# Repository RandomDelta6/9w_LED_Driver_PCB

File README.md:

# Introduction

This a power supply that feeds mains to power a 9w led array for general illumination (60W Incandescent equivalent). The circuit is based around the Sic 9752 microcontroller which provides Active PFC (Power Factor Correction) for high power factor and low THD. Its also a non isolated buck driver which allows it have >95% power efficiency and a simple compact circuit. It also features over current protection, over temperature protection, short circuit protection, low startup and operating current and flicker free continuous mode operation. It also incorporates QoL features such as soft start and a discharge resistor to ensure no ghost glow and fast cutoff when switched off.

# Schematic

# PCB

PCB Front View

PCB Back View

# Usage

Wave Solder all SMD components on the front side of the board. Then, thread in the THT components through their respective through holes from the back side and solder on to the front side. Snip off excess length of the legs after soldering. Solder a wire from +ve pad of LED grid to +ve output pad of this pcb. Solder a wire from -ve pad of LED grid to -ve output pad of this pcb. Thread in the wire through the hole from the back of the pcb and solder it on the front side.

For B22 Base, thread the free legs of the fusible resistors through the holes on the bottom of the base. Apply sufficient amount of solder to make the contact points for the bulb with the electrical socket. Snip off excess length of the legs after soldering. For E26/27 Base, solder one leg to the bottom contact of the base and solder the other leg to the side contact of the base.

This pcb is intended for LED bulbs with an opaque lower half body and translucent/ transparent cap (as pictured above) and not for the ones featuring a fully transparent or translucent body. This pcb is tuned for a 220V AC Power Input. This pcb expects a DOB grid of LED chips only, of 9W dissipation on the output and not a DOB board featuring other components (as illustrated above). DOB boards typically have an aluminimum substrate to aid in heat dissipation and are thermally coupled to an aluminium disc for larger thermal mass and surface area to aid in heat dissipation. The pcb must be suspended or have the front surface isolated by a layer of Kapton tape incase the opaque lower half of the bulb features aluminium plating for heat dissipation. The pcb must be completely isolated electrically from any other metal surfaces except as specified in the first paragraph of usage directions.

# Notes

Although I am pretty confident the board should work, please have the board verified by a professional before deploying in production. I am not particularly sure about the value of C5. C6 and R8 are not to be connected for intended use as a 9w LED Driver PCB.

Couldn't find a proper model for Inductor L2, so it is missing on the back view of the PCB. Didn't bother with it since it doesn't really matter much. Couldn't find the proper model for Film Capacitor C1. In reality it would look like a brown pillow with the same pin to pin footprint as in the back view of pcb.

This project was initially made with Kicad 5.1.10 and later updated on Kicad 7.0

While exporting for fabrication the back solder mask layer may be ignored to save on manufacturing costs as it serves no purpose.

# Disclaimer
This board has not been printed and tested physically to verify functionality. I do not assume any liability for the materials, information and opinions provided on, or available through, this project. I disclaim any liability for injury, death or damages resulting from the use thereof. This board is classified as “HOT” since it takes in mains power. Modify or work on it at your own risk and maintain proper safety procedures while physically handling such circuits.

# Licensing
All PCB design files and hardware are released under the [Creative Commons Attribution Share Alike 4.0 license](https://choosealicense.com/licenses/cc-by-sa-4.0/).

All other software is released under the [GNU General Public License v3.0](https://choosealicense.com/licenses/gpl-3.0/).

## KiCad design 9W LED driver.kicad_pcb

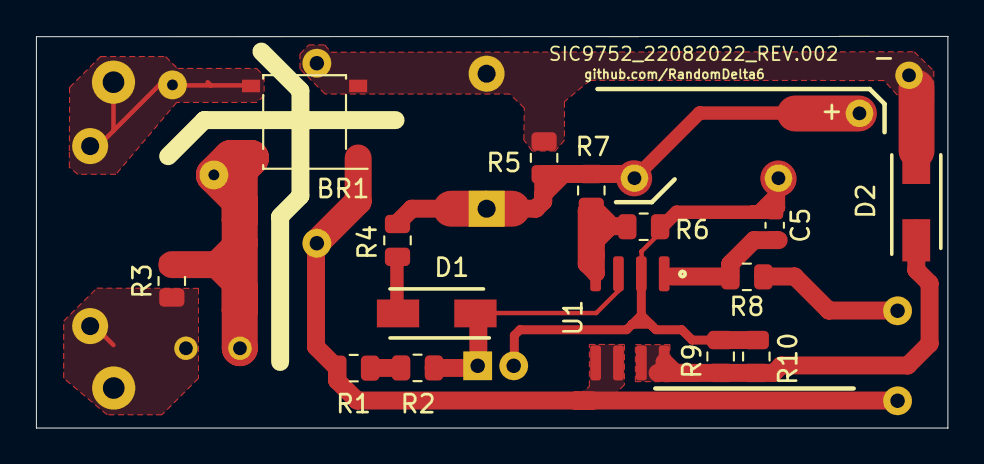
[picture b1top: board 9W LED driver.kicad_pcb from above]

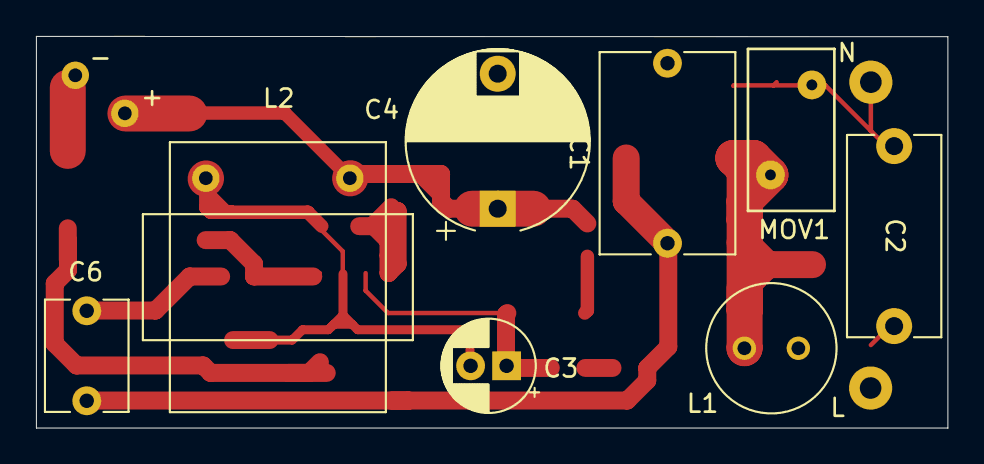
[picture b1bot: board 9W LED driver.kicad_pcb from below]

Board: 2 copper layers, 50.6 x 21.8 mm, 27 parts (10 on the bottom side), 14 nets.

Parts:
+: +ve Output; Pad
-: -ve Output; Pad
BR1: D_Bridge_+-AA; Diode_Bridge_Diotec_ABS
C1: 3.3uF 400V; C_Rect_L11.0mm_W7.3mm_P10.00mm_MKT
C2: 0.01uF 400V; C_Disc_D11.0mm_W5.0mm_P10.00mm
C3: 4.7uF 50V; CP_Radial_D5.0mm_P2.00mm
C4: 82uF 80V; CP_Radial_D10.0mm_P7.50mm
C5: 220nF 50V; C_0603_1608Metric
C6: C_Disc_D6.0mm_W4.4mm_P5.00mm
D1, D2: D ES1J; DIOM5227X250N
F1, F2: 56.00 ± 5%; R_Axial_DIN0411_L9.9mm_D3.6mm_P12.70mm_Horizontal
L1: 7mH; L_Radial_D7.0mm_P3.00mm
L2: 2.1mH; Inductor_Transformer
MOV1: 320V 100pF; RV_Disc_D9mm_W4.8mm_P5mm
R1, R2: 330K; R_0805_2012Metric
R3: 47K; R_0805_2012Metric
R4: 24K; R_0805_2012Metric
R5, R6: 150K; R_0805_2012Metric
R7: 210; R_0805_2012Metric
R8: R_0805_2012Metric
R9, R10: 3.3; R_0805_2012Metric
U1: Sic9752; SOIC-8_3.9x4.9mm_P1.27mm

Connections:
+ve_Rail: BR1.1 (+), C1.1, C6.2, R1.1, U1.5 (DRAIN), U1.6 (DRAIN)
+ve_output: +.1, C4.1, L2.1, R4.1, R5.1, R7.2
GNDS: -.1, BR1.2 (-), C1.2, C4.2, D2.2 (A), R5.2
unnamed: BR1.3, C2.2, F2.1, MOV1.1
unnamed: BR1.4, L1.2, MOV1.2, R3.2
unnamed: C2.1, F1.1, L1.1, R3.1
unnamed: C6.1, R8.1
unnamed: D1.2 (A), R4.2
unnamed: C3.1, D1.1 (K), R2.2, U1.3 (VDD)
unnamed: D2.1 (K), R9.1, R10.1, U1.7 (ISEN), U1.8 (ISEN)
unnamed: R1.2, R2.1
unnamed: C5.2, R8.2, U1.1 (COMP)
unnamed: R6.1, R7.1, U1.4 (FB)
unnamed: C3.2, C5.1, L2.2, R6.2, R9.2, R10.2, U1.2 (GND)

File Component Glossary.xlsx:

Sl. No. | Notation | Type | Description | Value | Particulars | Remarks
1 | BR1 | Bridge Rectifier | _+-AA | 1PHASE 1KV 800MA | MB10F 1/6K
2 | C1 | Capacitor | Film | 3.3uF 400V | CY400 473KE
3 | C2 | Capacitor | Ceramic/ Film | 68nF 275VAC |  | Optional - Noise Suppression
4 | C3 | Capacitor | Electrolytic | 4.7uF 50v
5 | C4 | Capacitor | Electrolytic | 82uF 80V
6 | C5 | Capacitor | SMD MLCC 0603 | 220nF 200VAC |  | Ripple Isolation - Connect either c6 or c5
7 | C6 | Capacitor | Ceramic/ Film | 220nF 200VAC |  | Optional - Noise Suppression
8 | D1 | Diode |  |  | ES1J
9 | D2 | Diode |  |  | ES1J
10 | F1 | Resistor | Metal film | 56ohm ± 5% | Fusible resistor | Protects against inrush current
11 | F2 | Resistor | Metal film | 56ohm ± 5% | Fusible resistor | Protects against inrush current
12 | IC1 | Controller | SMD DIP8 |  | SIC 9752 | Buck APFC Driver
13 | L1 | Inductor | Radial-cylinderical | 7mH | Choke Coil
14 | L2 | Inductor | EE10 | 2.1mH 200V | Transformer wound | Maintains power across leds on falling edge of current signal - Flicker free
15 | MOV1 | Varistor | Metal Oxide |  | MOV-07D511K 320V 100pF 10%
16 | R1 | Resistor | SMD 0805 | 330kΩ | 334
17 | R2 | Resistor | SMD 0805 | 330kΩ | 334
18 | R3 | Resistor | SMD 0805 | 47 kΩ | 473
19 | R4 | Resistor | SMD 0805 | 24 kΩ | 243
20 | R5 | Resistor | SMD 0805 | 150 kΩ | 154
21 | R6 | Resistor | SMD 0805 | 150 kΩ | 154
22 | R7 | Resistor | SMD 0805 | 210 Ω | 211
23 | R8 | Resistor | SMD 0805 | 24 kΩ | 243 | compensates for low esr, NC if C6 is NC
24 | R9 | Resistor | SMD 0805 | 3.3 Ω | 3R30
25 | R10 | Resistor | SMD 0805 | 3.3 Ω | 3R30

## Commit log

2022-08-19 Layout Fix
    Fixed Layout issues and updated Silkscreen
2022-08-25 refined design
2023-01-26 fixed layout conflicts
2023-01-26 updated libs
2023-01-30 library update
2023-01-30 Updated Schematics
2023-01-31 Updated PCB Layout
2023-02-03 pcb revision
2023-02-03 Create LICENSE
2023-02-09 Schematic Correction
2023-04-11 Fixed Schematic and Updated PCB
2023-04-11 refine pcb layout
